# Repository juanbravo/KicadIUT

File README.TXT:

Etape1: créer la structure de vos dossiers
Il est conseillé d'organiser vos dossiers comme suit:
Kicad--- MesProjets
	|
	-KicadIUT
Pour cela créer Kicad et DEZIPPER l'archive KicadIUT
		
Etape1: choisir un template (dans BoardTemplate) à copier ensuite dans MesProjets
	Quel template choisir?
		template_a_renommer = juste une structure de dossier - projet à créer
		template_shield_arduino_uno_R3= création d'un shield UNO R3
		template_nano_board = création d'une carte autour d'une nanao board
		ATMega328P_Template1.0= création d'une carte micro autour d'un ATMEGA328P
		
Etape2: renommer le dossier copié

Etape3: lancer le script rename.py (vois readme à l'intérieur des templates)

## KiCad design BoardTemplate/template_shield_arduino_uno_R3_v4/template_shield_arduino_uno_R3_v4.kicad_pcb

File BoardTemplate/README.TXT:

Etape1: choisir un template (dans BoardTemplate) à copier ensuite dans VosProjets
	Quel template
		template_a_renommer = juste une structure de dossier - projet à créer
		template_shield_arduino_uno_R3= création d'un shield UNO R3
		template_nano_board = création d'une carte autour d'une nanao board
		ATMega328P_Template1.0= création d'une carte micro autour d'un ATMEGA328P
		
Etape2: renommer le dossier copié

Etape3: lancer le script rename.py (vois readme à l'intérieur des template)

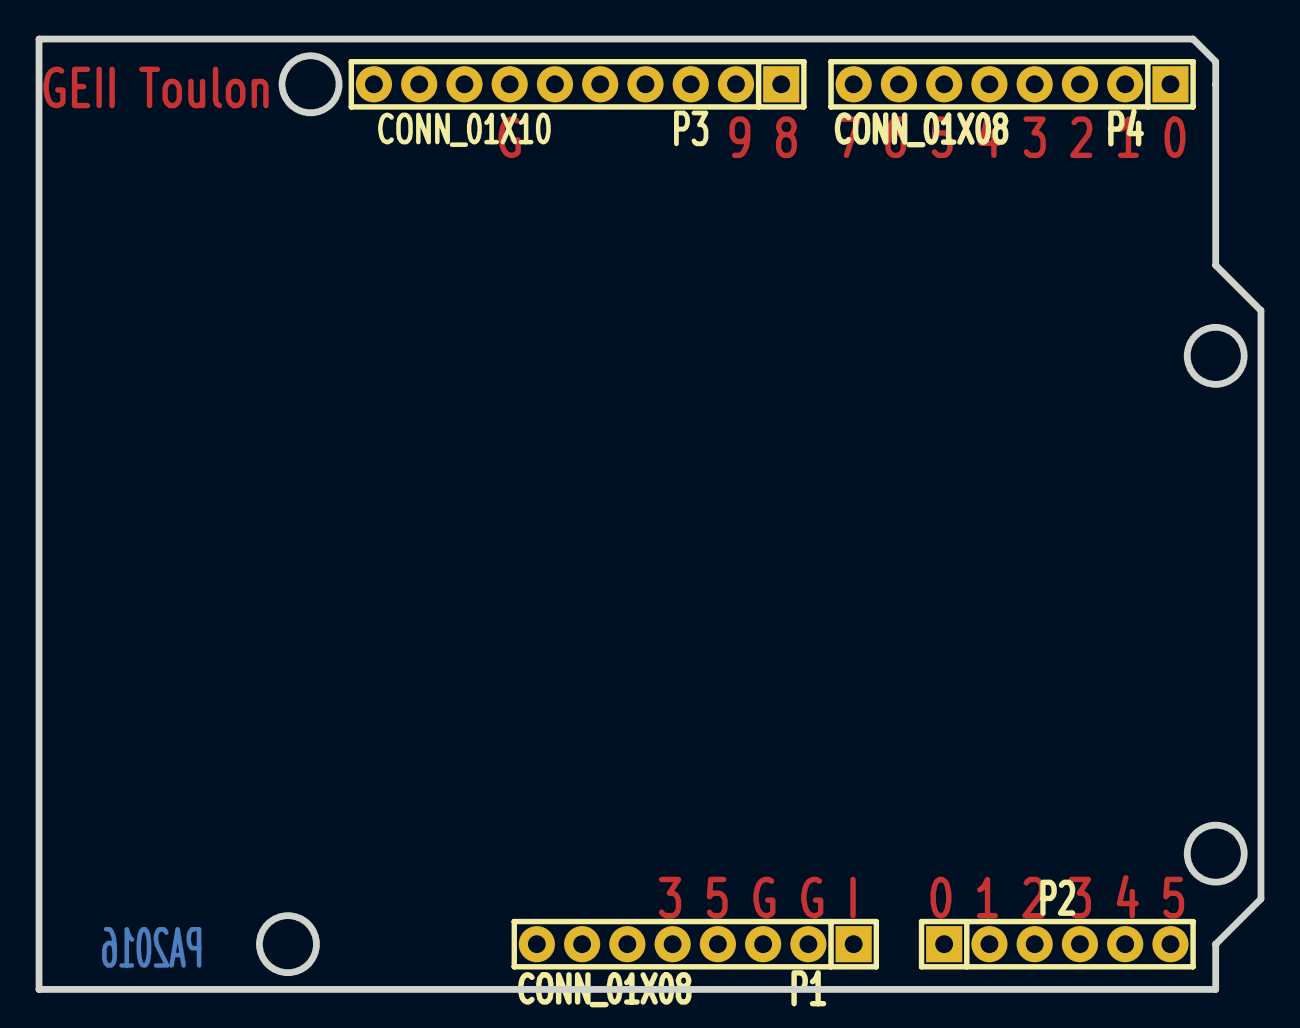
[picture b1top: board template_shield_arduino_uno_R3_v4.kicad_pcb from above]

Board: 2 copper layers, 68.6 x 53.3 mm, 4 parts (0 on the bottom side), 3 nets, no tracks yet.

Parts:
P1, P4: CONN_01X08; IUT-SIL-8
P2: CONN_01X06; IUT-SIL-6
P3: CONN_01X10; IUT-SIL-10

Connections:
/AD4/SDA: P2.5, P3.9
/AD5/SCL: P2.6, P3.10
GND: P1.2, P1.3, P3.7

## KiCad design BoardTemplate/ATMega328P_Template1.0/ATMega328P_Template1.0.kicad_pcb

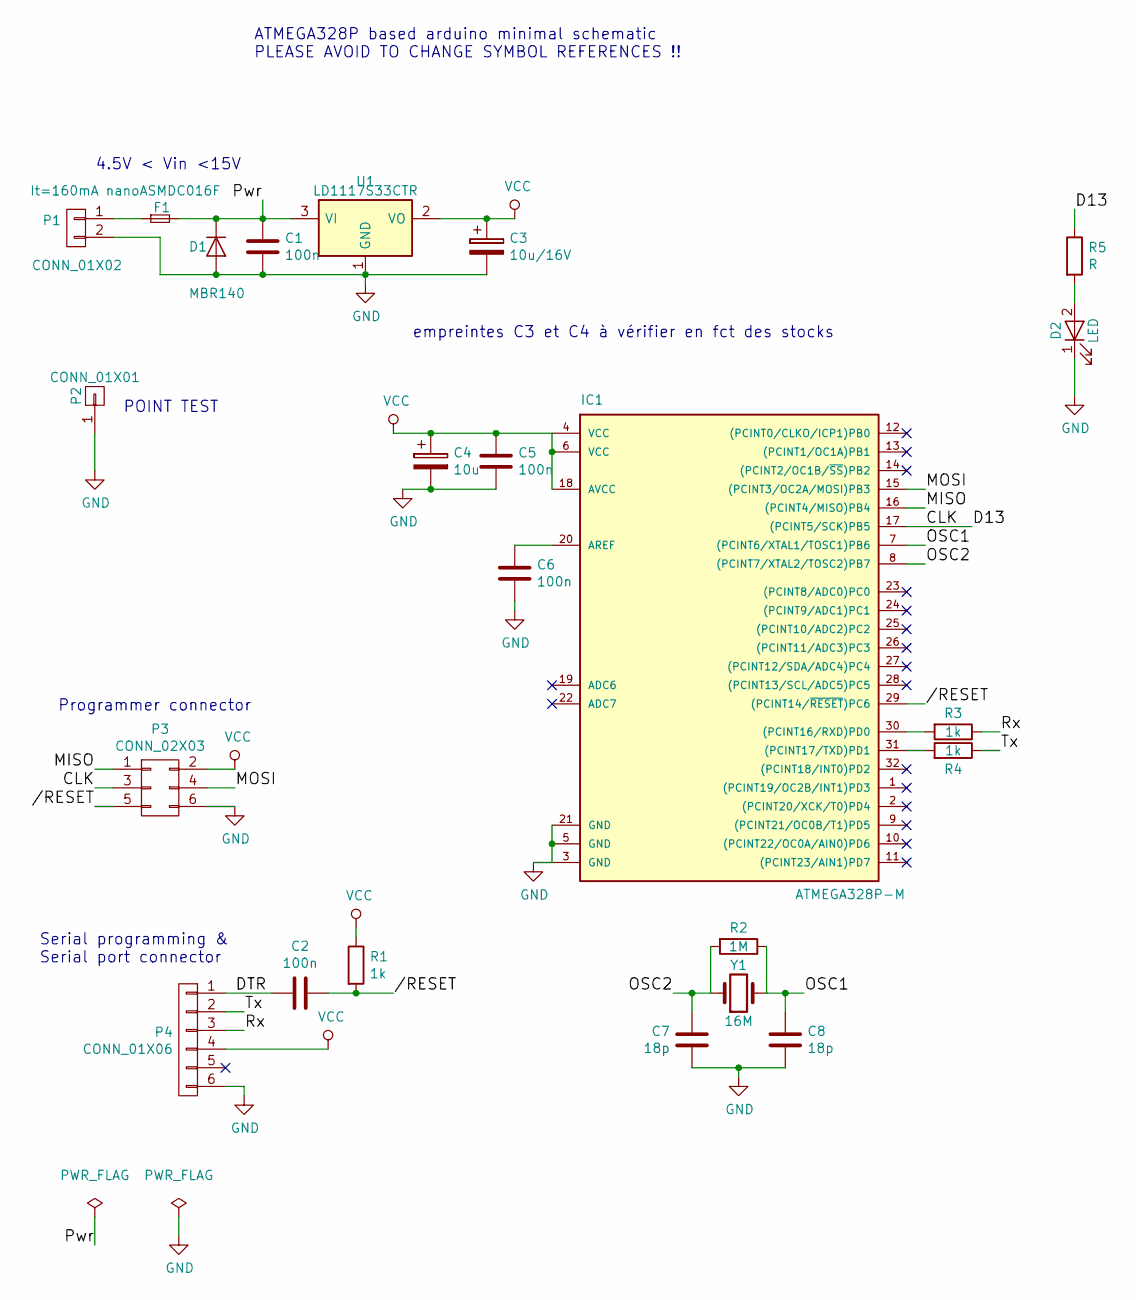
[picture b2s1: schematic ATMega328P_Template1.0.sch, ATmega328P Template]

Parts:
C1, C2, C5, C6: 100n; C_0805
C3: 10u/16V; C_0805
C4: 10u; C_0805
C7, C8: 18p; C_0805
D1: MBR140; MiniMELF_Handsoldering
D2: LED; LED_0805
F1: It=160mA nanoASMDC016F; SMD-1210_Pol
IC1: ATMEGA328P-M; TQFP-32_7x7mm_Pitch0.8mm
P1: CONN_01X02; IUT-bornier2
P2: CONN_01X01; IUT-1pin
P3: CONN_02X03; IUT-conn_3x2
P4: CONN_01X06; IUT-SIL-6
R1, R3, R4: 1k; R_0805
R2: 1M; R_0805
R5: R; R_0805
U1: LD1117S33CTR; SOT-223
Y1: 16M; IUT-Crystal_HC49-SD_SMD_RevA_09Aug2010

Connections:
//RESET: C2.1, IC1.29 ((PCINT14/~RESET~)PC6), P3.5, R1.2
/CLK: IC1.17 ((PCINT5/SCK)PB5), P3.3, R5.1
/DTR: C2.2, P4.1
/MISO: IC1.16 ((PCINT4/MISO)PB4), P3.1
/MOSI: IC1.15 ((PCINT3/OC2A/MOSI)PB3), P3.4
/OSC1: C8.1, IC1.7 ((PCINT6/XTAL1/TOSC1)PB6), R2.1, Y1.2
/OSC2: C7.2, IC1.8 ((PCINT7/XTAL2/TOSC2)PB7), R2.2, Y1.1
/Pwr: C1.1, D1.1 (K), F1.2, U1.3 (VI)
/Rx: P4.3, R3.1
/Tx: P4.2, R4.1
GND: C1.2, C3.2, C4.2, C5.2, C6.2, C7.1, C8.2, D1.2 (A), D2.1 (K), IC1.3 (GND), IC1.5 (GND), IC1.21 (GND), P1.2, P2.1, P3.6, P4.6, U1.1 (GND)
unnamed: C6.1, IC1.20 (AREF)
unnamed: D2.2 (A), R5.2
unnamed: F1.1, P1.1
unnamed: IC1.30 ((PCINT16/RXD)PD0), R3.2
unnamed: IC1.31 ((PCINT17/TXD)PD1), R4.2
VCC: C3.1, C4.1, C5.1, IC1.4 (VCC), IC1.6 (VCC), IC1.18 (AVCC), P3.2, P4.4, R1.1, U1.2 (VO)

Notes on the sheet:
ATMEGA328P based arduino minimal schematic PLEASE AVOID TO CHANGE SYMBOL REFERENCES !!
Programmer connector
Serial programming & Serial port connector
4.5V < Vin <15V
POINT TEST
empreintes C3 et C4 à vérifier en fct des stocks

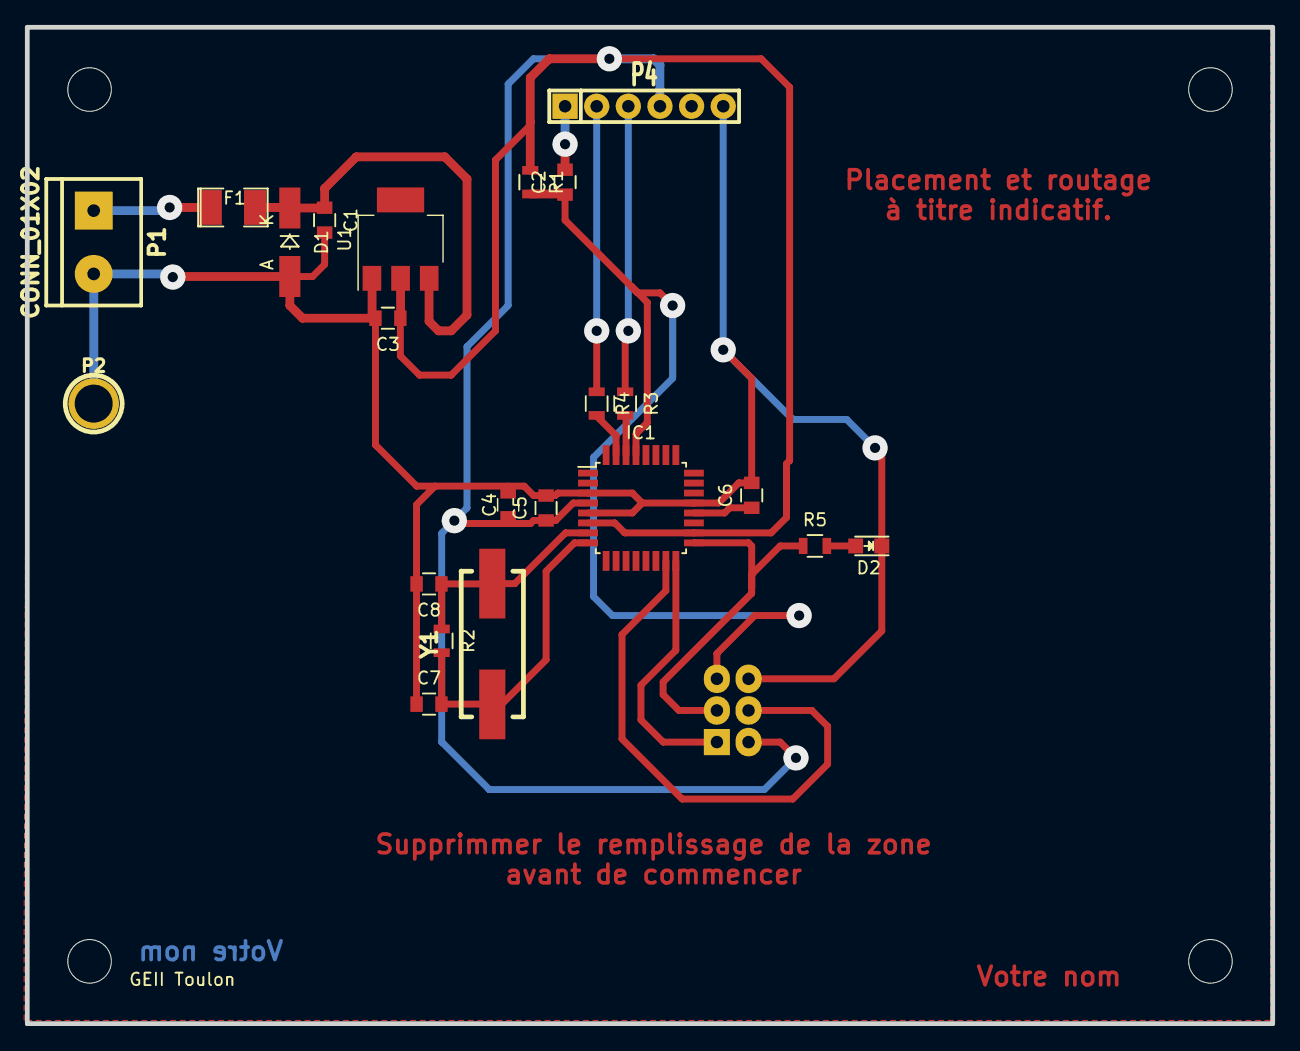
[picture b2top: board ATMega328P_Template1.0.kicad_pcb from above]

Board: 2 copper layers, 100.0 x 80.0 mm, 24 parts (1 on the bottom side), 17 nets.

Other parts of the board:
GEII Toulon : EuroBoard_halb_Type-I_100mmX80mm_holes

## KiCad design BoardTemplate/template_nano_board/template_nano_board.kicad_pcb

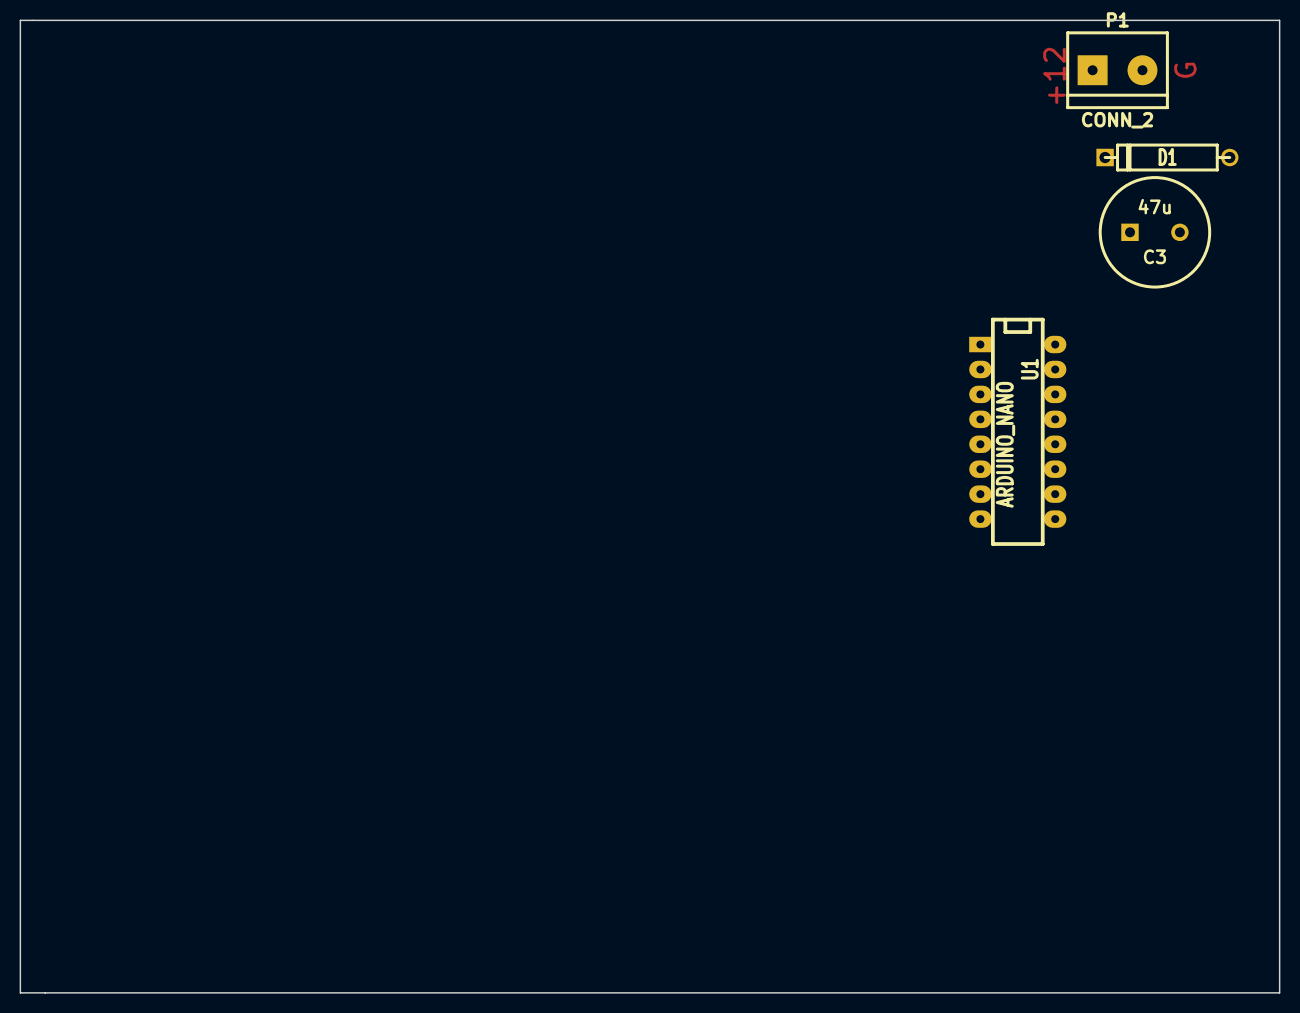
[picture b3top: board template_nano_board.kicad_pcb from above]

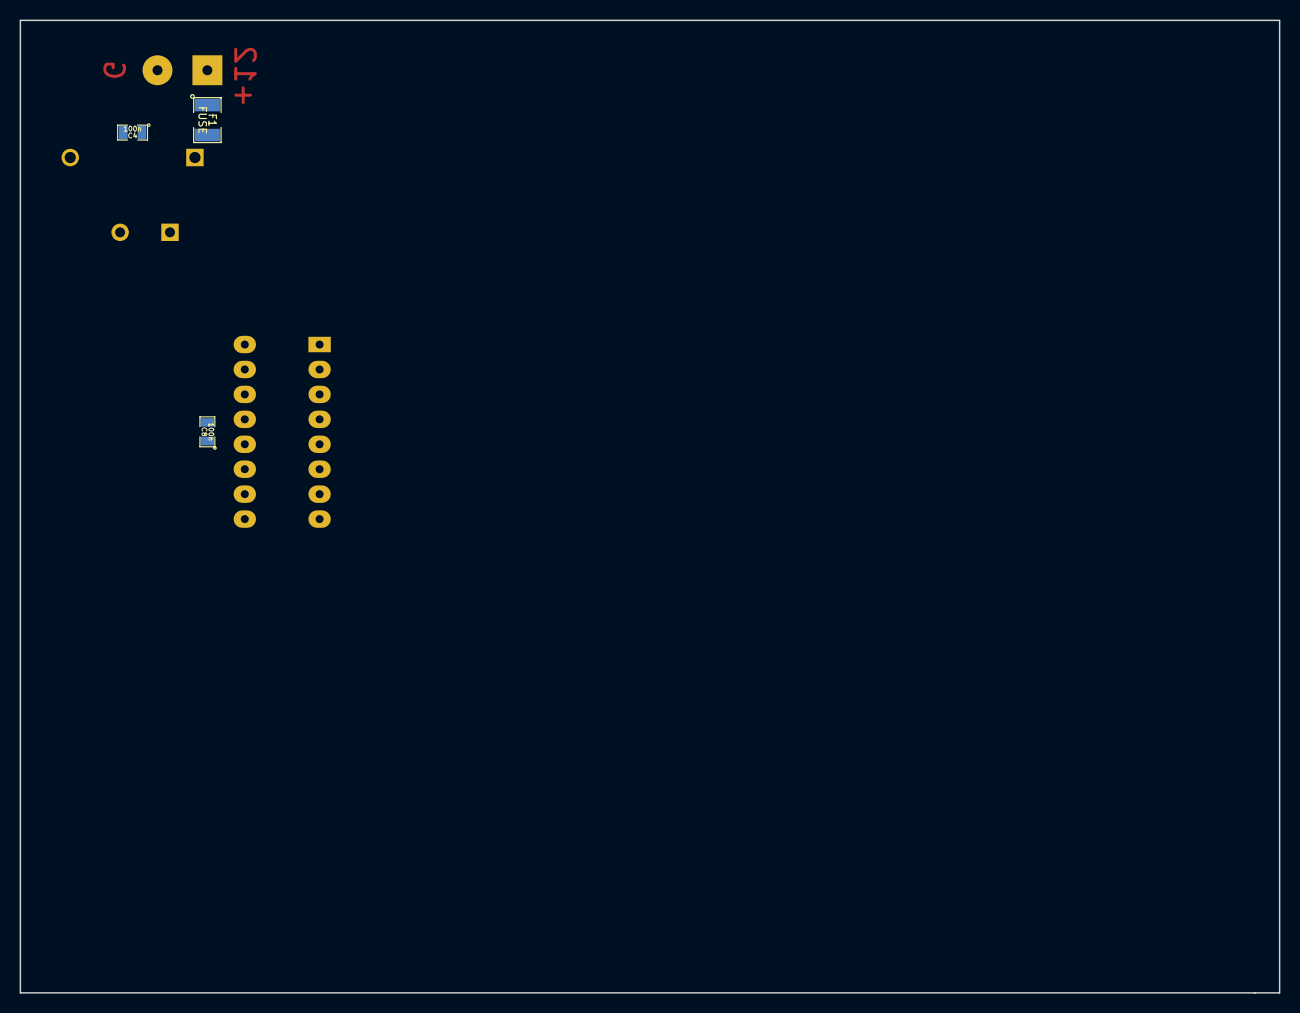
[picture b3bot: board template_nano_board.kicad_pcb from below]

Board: 2 copper layers, 128.3 x 99.1 mm, 7 parts (3 on the bottom side), 5 nets, no tracks yet.

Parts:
C3: 47u; C2V10
C4, C8: 100n; SM0805
D1: DIODE; D5
F1: FUSE; SM1210
P1: CONN_2; IUT-bornier2
U1: ARDUINO_NANO; IUT-DIP_16__300_ELL

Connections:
+5V: C8.1, U1.12
+12F: C3.1, C4.1, D1.2, F1.2, U1.15
+12V: F1.1, P1.1
GND: C8.2, U1.14
unnamed: C3.2, C4.2, D1.1, P1.2

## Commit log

2017-04-05 initial-mise à jour Kicad v4
